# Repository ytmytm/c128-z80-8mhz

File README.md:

# C128 and 8MHz Z80

With a simple daughterboard, a GAL and a 74LS74 the Z80 in C128 can run at dot clock frequency (almost 8MHz) during its 1MHz phase of the system clock, effectively doubling the speed.

Basic benchmarks written in Turbo Pascal show that indeed it is about twice faster.

CP/M is visibly snappier, to the point of being usable.

This circuit works fine, during tests it was stable for several hours, busy with drawing fractals and calculating pi using Monte-Carlo method.

The CPU doesn't even get warm to the touch.

Disk I/O worked fine, as well as REU ram disk M: (emulated by UII+).

## BACKGROUND

There was a message sent to [cbm-hackers mailing list](https://www.softwolves.com/arkiv/cbm-hackers/7/7361.html) back in 2002, about a PCB for C128 that boosted Z80 to 8MHz

Unfortunately that device was not fully reverse-engineered and it seems that it was never mentioned again.

## PREPARING C128

I haven't tried to overclock the original Z80B, I replaced it some time ago by a Z84C0020 that uses much less energy.

Following modifications can be done using bending Z80 pins and soldering to the mainboard, but having a daughterboard will keep everything tidy.

We need to isolate `/WAIT` input (pin 24) from the mainboard because it is tied to `/NMI` there.
We will also disconnected from CPU the onboard `CLK` signal (pin 6).
We will use it as an GAL input to have an option of switching between the original clock (4MHz half of the time) and fast mode (8MHz half of the time).
The new `CLK` will be generated by GAL. We will also use few other lines from Z80 as GAL inputs.

We need two more inputs not available on the Z80 chip/Z80 socket. We want `DOT CLOCK` from the expansion port (pin 6) and the system clock 1MHz signal
(called `CLK1MHZ` below and `D1MHZ` on C128 schematic) from U12 (pin 11).

## OPERATION

This is the normal timing of Z80 in C128. During system clock `CLK1MHZ` low phase VIC generates two clock ticks for Z80.

We use `DOT CLOCK` instead to pass four ticks.

Whenever Z80 wants to read or write to/from memory or I/O we have to stop it until the start of the next 1MHz clock low phase.

Latched data from 74LS74 will hold the `/WAIT` line low until the end of current low phase of `CLK1MHZ` (Z80 turn).
During the following high phase (VIC's turn) 74LS74 will stay in reset and release `WAIT` to inactive (high) state, but during that time we will not output any clock pulses - just like in the original setup.

I had to add a case to `CLKOUT` to handle memory writes. Waitstate is not enough, the CPU had to be really stopped. That's not an issue for reads because they are buffered with U12.

Here is the effect - for two clocks Z80 was running at 1MHz because of memory write, then picked up the speed:

## CIRCUIT

The Kicad project is in [z80-dotclock-gal-and-latch/](z80-dotclock-gal-and-latch) folder.

Schematic is also [available in PDF form](z80-dotclock-gal-and-latch/plots/z80-dot-gal.pdf).

## PCB

Gerber files generated from PCB project that should fit C128 and C128DCR are in  [z80-dotclock-gal-and-latch/gerbers/](z80-dotclock-gal-and-latch/gerbers) folder.

## LOGIC EQUATIONS

PLD file to be used with WinCUPL to generate JED file for programming GAL is available in two versions:

- for 22V10 in [z80-dotclock-gal-and-latch/gal22v10/](z80-dotclock-gal-and-latch/gal22v10/)
- for 16V8 in [z80-dotclock-gal-and-latch/gal6v8/](z80-dotclock-gal-and-latch/gal16v8/)

You will find there all the files generated by WinCUPL, including JED files ready to be flased to GAL devices.

They differ only in pin numbering. I just happened to have an ATF22V10 available.
The circuit is ready for both options - just align pin 1 of 16V8 with pin 1 of the socket.

### 74LS74 and bus timing

Here is how it is supposed to work:

0. VIC cycle phase starts, latch is in reset state, latch `D` input is
   constant `1`, but due to reset `Q` output is `0` and negated `/Q` is `1`; Z80 is
   stopped as its clock is held low
1. Z80 cycle phase starts, latch goes out of reset, `/Q` output = `WAITLATCH`
   stays `1`, Z80 sees that as inactive `/WAIT` and runs program, without bus
   access requests `WAITTRIGGER` stays `0`
2. Z80 wants to access the bus, `WAITTRIGGER` will rise to `1`; this will cause
   latch D input connected to `1` be copied to the output, so `/Q` becomes `0`, Z80
   will see that as an active `/WAIT` and will stop
3. This state will not change until start of the next VIC cycle phase
4. VIC cycle phase starts, latch is reset - will set latch `/Q` to `1`, so for
   Z80 `/WAIT` now becomes inactive; but Z80 won't run because during this
   half-cycle the CPU clock signal is not passed at all
5. Z80 cycle phase starts, it can continue because after latch reset `/WAIT`
   is inactive; Z80 accesses the bus so `WAITTRIGGER` stays `1` until Z80 gets
   what it needs from data lines - then it goes back to `0`

The idea of this is that during Z80 clock phase when `WAITTRIGGER` goes from
inactive to active we can latch `/WAIT` line low to hold it low at least
until the start of VIC cycle.

We release it before/at the start of Z80 cycle it so `/WAIT` becomes high
again - even though the latch trigger condition is still active.

### CLKOUT
The simplest way to handle CLKOUT I did was:
```
  CLKOUT = !DOTCLK & !CLK1MHZ;
```
C128 started fine, but CP/M wouldn't boot. With pieces of Z80 code I was able to confirm that this works for I/O reads and writes but only memory reads.
Memory writes never happened, hence the special case with `MREQ & WR`. 

## 16MHZ?

I tried using the 16MHz clock signal from VDC (pin 2) instead of dot clock.

The C128 will start, but CP/M won't boot. However all my simple tests passed.
I suspect that memory access is still an issue and some of the memory writes fail.

A possible reason is that exact 16MHz signal is not a true double of the dot clock, which depends on PAL/NTSC.

If this is the reason, then one solution could be to [double the dot clock using MAX9010](https://www.analog.com/en/resources/design-notes/simple-circuit-doubles-input-frequency.html).
This idea was [already mentioned on Reddit](https://www.reddit.com/r/c128/comments/9judf7/z80_possible_clockdoubling_mitigation_against/), but that circuit would never work.
But it depends on specific values of R/C pair.

Using a part [specifically designed for that purpose - ICS501](https://www.renesas.com/us/en/document/dst/501-datasheet) seems more reliable.

## OPEN QUESTIONS

1) How can we keep it simple but run at full speed all the time and stall only on memory and I/O access? It's not clear if the device mentioned in 2002 was really working at 8MHz all the time or just during Z80's turn.

2) Since I already used ATF22V10 which has asynchronous reset for registers, it should be possible to get rid of 74LS74 with different assignment of pin 1 (GAL CLK input). I wasn't able to do it.
   I'm probably doing something wrong - messing up high/low vs active/inactive or my CUPL skills are lacking (they are).

3) What is the problem with 16MHz clock? Maybe it should be created by doubling the dot clock to keep things in sync? (No need to bother if (1) is possible).

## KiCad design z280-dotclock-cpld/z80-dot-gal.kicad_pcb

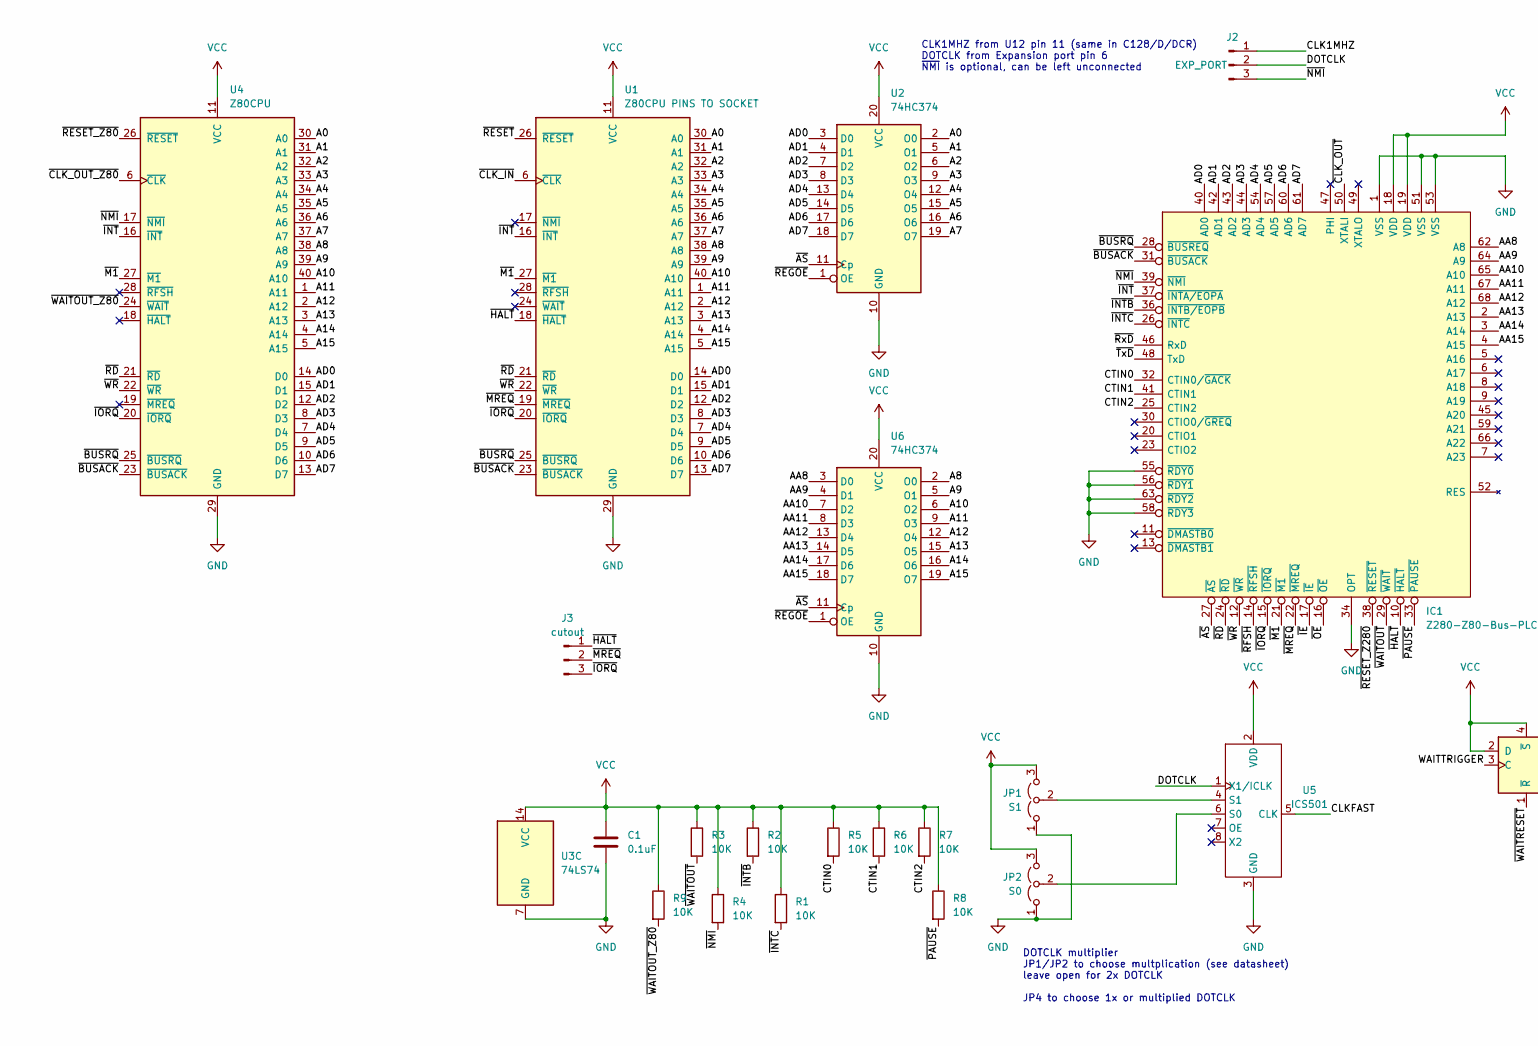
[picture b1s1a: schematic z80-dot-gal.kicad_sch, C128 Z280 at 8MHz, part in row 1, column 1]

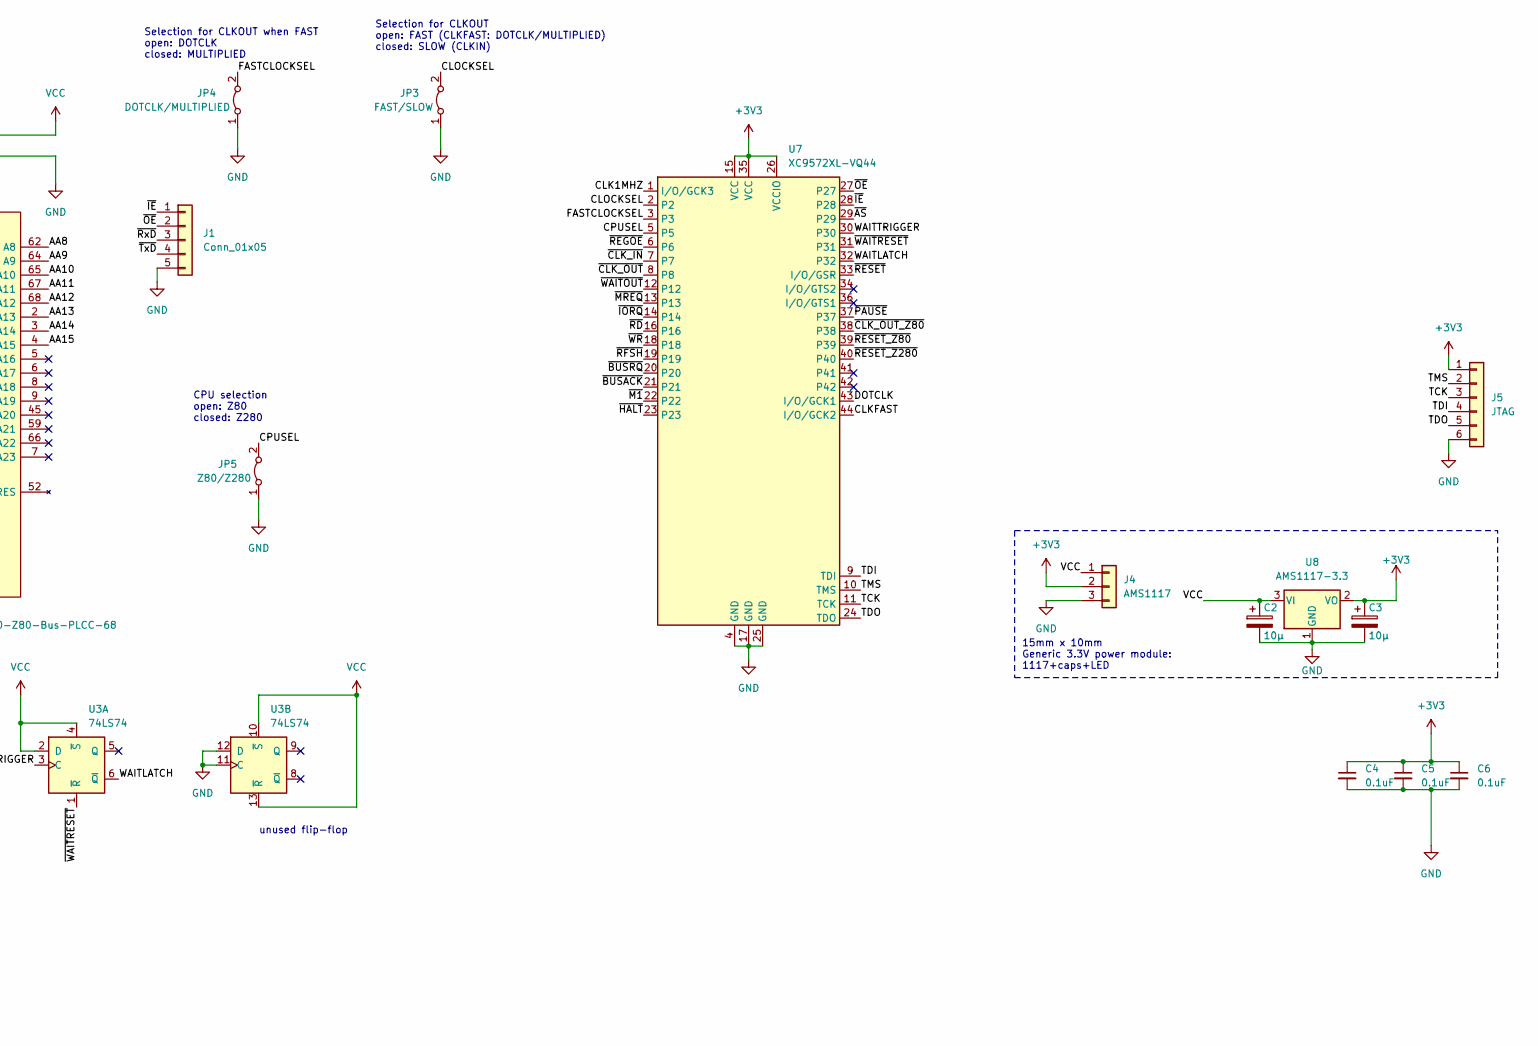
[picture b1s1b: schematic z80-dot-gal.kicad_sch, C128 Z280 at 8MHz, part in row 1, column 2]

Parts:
C1: 0.1uF; C_Disc_D8.0mm_W2.5mm_P5.00mm
C2, C3: 10µ; CP_EIA-3216-12_Kemet-S_HandSolder; JLCPCB Part # C1969735
C4, C5, C6: 0.1uF; C_0805_2012Metric_Pad1.18x1.45mm_HandSolder; JLCPCB Part # C49678
IC1: Z280-Z80-Bus-PLCC-68; PLCC-68_THT-Socket; Manufacturer_Part_Number Z8S18033VSG; Mouser Part Number 692-Z8S18033VSG
J1: Conn_01x05; PinHeader_1x05_P2.54mm_Vertical
J2: EXP_PORT; PinHeader_1x03_P2.54mm_Vertical
J3: cutout; PinHeader_1x03_P2.54mm_Vertical
J4: AMS1117; PinHeader_1x03_P2.54mm_Vertical
J5: JTAG; PinHeader_1x06_P2.54mm_Vertical
JP1: S1; PinHeader_1x03_P2.54mm_Vertical
JP2: S0; PinHeader_1x03_P2.54mm_Vertical
JP3: FAST/SLOW; PinHeader_1x02_P2.54mm_Vertical
JP4: DOTCLK/MULTIPLIED; PinHeader_1x02_P2.54mm_Vertical
JP5: Z80/Z280; PinHeader_1x02_P2.54mm_Vertical
R1, R2, R3, R4, R5, R6, R7, R8, R9: 10K; R_0805_2012Metric_Pad1.20x1.40mm_HandSolder
U1: Z80CPU PINS TO SOCKET; DIP-40_W15.24mm_Socket_LongPads
U2, U6: 74HC374; DIP-20_W7.62mm
U3: 74LS74; DIP-14_W7.62mm_Socket
U4: Z80CPU; DIP-40_W15.24mm_Socket_LongPads
U5: ICS501; SOIC-8_3.9x4.9mm_P1.27mm
U7: XC9572XL-VQ44; TQFP-44_10x10mm_P0.8mm
U8: AMS1117-3.3; SOT-223-3_TabPin2; JLCPCB Part # C6186

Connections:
+3V3: C3.1, C4.1, C5.1, C6.1, J4.2, J5.1, U7.15 (VCC), U7.26 (VCCIO), U7.35 (VCC), U8.2 (VO)
/A0: U1.30 (A0), U2.2 (O0), U4.30 (A0)
/A1: U1.31 (A1), U2.5 (O1), U4.31 (A1)
/A2: U1.32 (A2), U2.6 (O2), U4.32 (A2)
/A3: U1.33 (A3), U2.9 (O3), U4.33 (A3)
/A4: U1.34 (A4), U2.12 (O4), U4.34 (A4)
/A5: U1.35 (A5), U2.15 (O5), U4.35 (A5)
/A6: U1.36 (A6), U2.16 (O6), U4.36 (A6)
/A7: U1.37 (A7), U2.19 (O7), U4.37 (A7)
/A8: U1.38 (A8), U4.38 (A8), U6.2 (O0)
/A9: U1.39 (A9), U4.39 (A9), U6.5 (O1)
/A10: U1.40 (A10), U4.40 (A10), U6.6 (O2)
/A11: U1.1 (A11), U4.1 (A11), U6.9 (O3)
/A12: U1.2 (A12), U4.2 (A12), U6.12 (O4)
/A13: U1.3 (A13), U4.3 (A13), U6.15 (O5)
/A14: U1.4 (A14), U4.4 (A14), U6.16 (O6)
/A15: U1.5 (A15), U4.5 (A15), U6.19 (O7)
/AA8: IC1.62 (A8), U6.3 (D0)
/AA9: IC1.64 (A9), U6.4 (D1)
/AA10: IC1.65 (A10), U6.7 (D2)
/AA11: IC1.67 (A11), U6.8 (D3)
/AA12: IC1.68 (A12), U6.13 (D4)
/AA13: IC1.2 (A13), U6.14 (D5)
/AA14: IC1.3 (A14), U6.17 (D6)
/AA15: IC1.4 (A15), U6.18 (D7)
/AD0: IC1.40 (AD0), U1.14 (D0), U2.3 (D0), U4.14 (D0)
/AD1: IC1.42 (AD1), U1.15 (D1), U2.4 (D1), U4.15 (D1)
/AD2: IC1.43 (AD2), U1.12 (D2), U2.7 (D2), U4.12 (D2)
/AD3: IC1.44 (AD3), U1.8 (D3), U2.8 (D3), U4.8 (D3)
/AD4: IC1.54 (AD4), U1.7 (D4), U2.13 (D4), U4.7 (D4)
/AD5: IC1.57 (AD5), U1.9 (D5), U2.14 (D5), U4.9 (D5)
/AD6: IC1.60 (AD6), U1.10 (D6), U2.17 (D6), U4.10 (D6)
/AD7: IC1.61 (AD7), U1.13 (D7), U2.18 (D7), U4.13 (D7)
/CLK1MHZ: J2.1, U7.1 (I/O/GCK3)
/CLKFAST: U5.5 (CLK), U7.44 (I/O/GCK2)
/CLOCKSEL: JP3.2 (B), U7.2
/CPUSEL: JP5.2 (B), U7.5
/CTIN0: IC1.32 (CTIN0/~GACK), R5.2
/CTIN1: IC1.41 (CTIN1), R6.2
/CTIN2: IC1.25 (CTIN2), R7.2
/DOTCLK: J2.2, U5.1 (X1/ICLK), U7.43 (I/O/GCK1)
/FASTCLOCKSEL: JP4.2 (B), U7.3
/TCK: J5.3, U7.11 (TCK)
/TDI: J5.4, U7.9 (TDI)
/TDO: J5.5, U7.24 (TDO)
/TMS: J5.2, U7.10 (TMS)
/WAITLATCH: U3.6 (~Q), U7.32
/WAITTRIGGER: U3.3 (C), U7.30
/~AS: IC1.27 (~AS), U2.11 (Cp), U6.11 (Cp), U7.29
/~BUSACK: IC1.31 (~BUSACK), U1.23 (~BUSACK), U4.23 (~BUSACK), U7.21
/~BUSRQ: IC1.28 (~BUSREQ), U1.25 (~BUSRQ), U4.25 (~BUSRQ), U7.20
/~CLK_IN: U1.6 (~CLK), U7.7
/~CLK_OUT_Z80: U4.6 (~CLK), U7.38
/~CLK_OUT: IC1.50 (XTALI), U7.8
/~HALT: IC1.10 (~HALT), J3.1, U1.18 (~HALT), U7.23
/~IE: IC1.17 (~IE), J1.1, U7.28
/~INTB: IC1.36 (~INTB/EOPB), R2.2
/~INTC: IC1.26 (~INTC), R1.2
/~INT: IC1.37 (~INTA/EOPA), U1.16 (~INT), U4.16 (~INT)
/~IORQ: IC1.15 (~IORQ), J3.3, U1.20 (~IORQ), U4.20 (~IORQ), U7.14
/~M1: IC1.21 (~M1), U1.27 (~M1), U4.27 (~M1), U7.22
/~MREQ: IC1.22 (~MREQ), J3.2, U1.19 (~MREQ), U7.13
/~NMI: IC1.39 (~NMI), J2.3, R4.2, U4.17 (~NMI)
/~OE: IC1.16 (~OE), J1.2, U7.27
/~PAUSE: IC1.33 (~PAUSE), R8.2, U7.37
/~RD: IC1.24 (~RD), U1.21 (~RD), U4.21 (~RD), U7.16
/~REGOE: U2.1 (OE), U6.1 (OE), U7.6
/~RESET_Z80: U4.26 (~RESET), U7.39
/~RESET_Z280: IC1.38 (~RESET), U7.40
/~RESET: U1.26 (~RESET), U7.33 (I/O/GSR)
/~RFSH: IC1.14 (~RFSH), U7.19
/~RxD: IC1.46 (RxD), J1.3
/~TxD: IC1.48 (TxD), J1.4
/~WAITOUT_Z80: R9.2, U4.24 (~WAIT)
/~WAITOUT: IC1.29 (~WAIT), R3.2, U7.12
/~WAITRESET: U3.1 (~R), U7.31
/~WR: IC1.12 (~WR), U1.22 (~WR), U4.22 (~WR), U7.18
GND: C1.2, C2.2, C3.2, C4.2, C5.2, C6.2, IC1.1 (VSS), IC1.34 (OPT), IC1.51 (VSS), IC1.53 (VSS), IC1.55 (~RDY0), IC1.56 (~RDY1), IC1.58 (~RDY3), IC1.63 (~RDY2), J1.5, J4.3, J5.6, JP1.1 (A), JP2.1 (A), JP3.1 (A), JP4.1 (A), JP5.1 (A), U1.29 (GND), U2.10 (GND), U3.7 (GND), U3.11 (C), U3.12 (D), U4.29 (GND), U5.3 (GND), U6.10 (GND), U7.4 (GND), U7.17 (GND), U7.25 (GND), U8.1 (GND)
unnamed: JP1.2 (C), U5.4 (S1)
unnamed: JP2.2 (C), U5.6 (S0)
VCC: C1.1, C2.1, IC1.18 (VDD), IC1.19 (VDD), J4.1, JP1.3 (B), JP2.3 (B), R1.1, R2.1, R3.1, R4.1, R5.1, R6.1, R7.1, R8.1, R9.1, U1.11 (VCC), U2.20 (VCC), U3.2 (D), U3.4 (~S), U3.10 (~S), U3.13 (~R), U3.14 (VCC), U4.11 (VCC), U5.2 (VDD), U6.20 (VCC), U8.3 (VI)

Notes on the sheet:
CLK1MHZ from U12 pin 11 (same in C128/D/DCR) DOTCLK from Expansion port pin 6 ~{NMI} is optional, can be left unconnected
15mm x 10mm Generic 3.3V power module: 1117+caps+LED
DOTCLK multiplier JP1/JP2 to choose multplication (see datasheet) leave open for 2x DOTCLK JP4 to choose 1x or multiplied DOTCLK
CPU selection open: Z80 closed: Z280
Selection for CLKOUT open: FAST (CLKFAST: DOTCLK/MULTIPLIED) closed: SLOW (CLKIN)
unused flip-flop
Selection for CLKOUT when FAST open: DOTCLK closed: MULTIPLIED

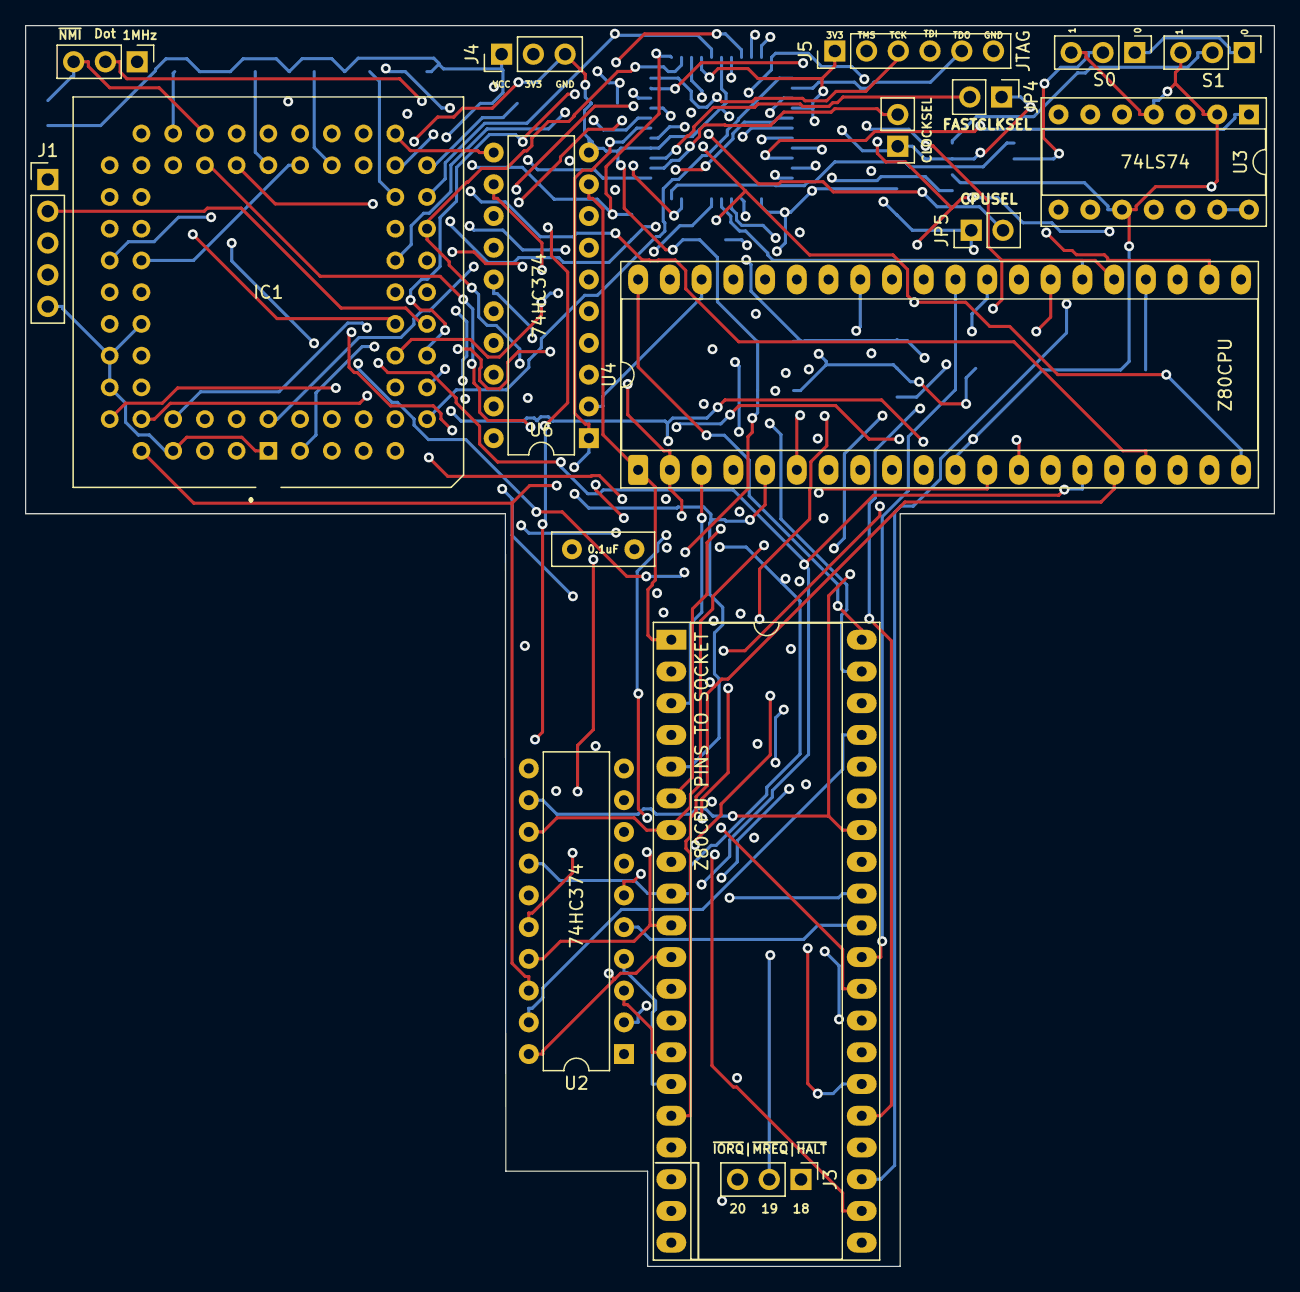
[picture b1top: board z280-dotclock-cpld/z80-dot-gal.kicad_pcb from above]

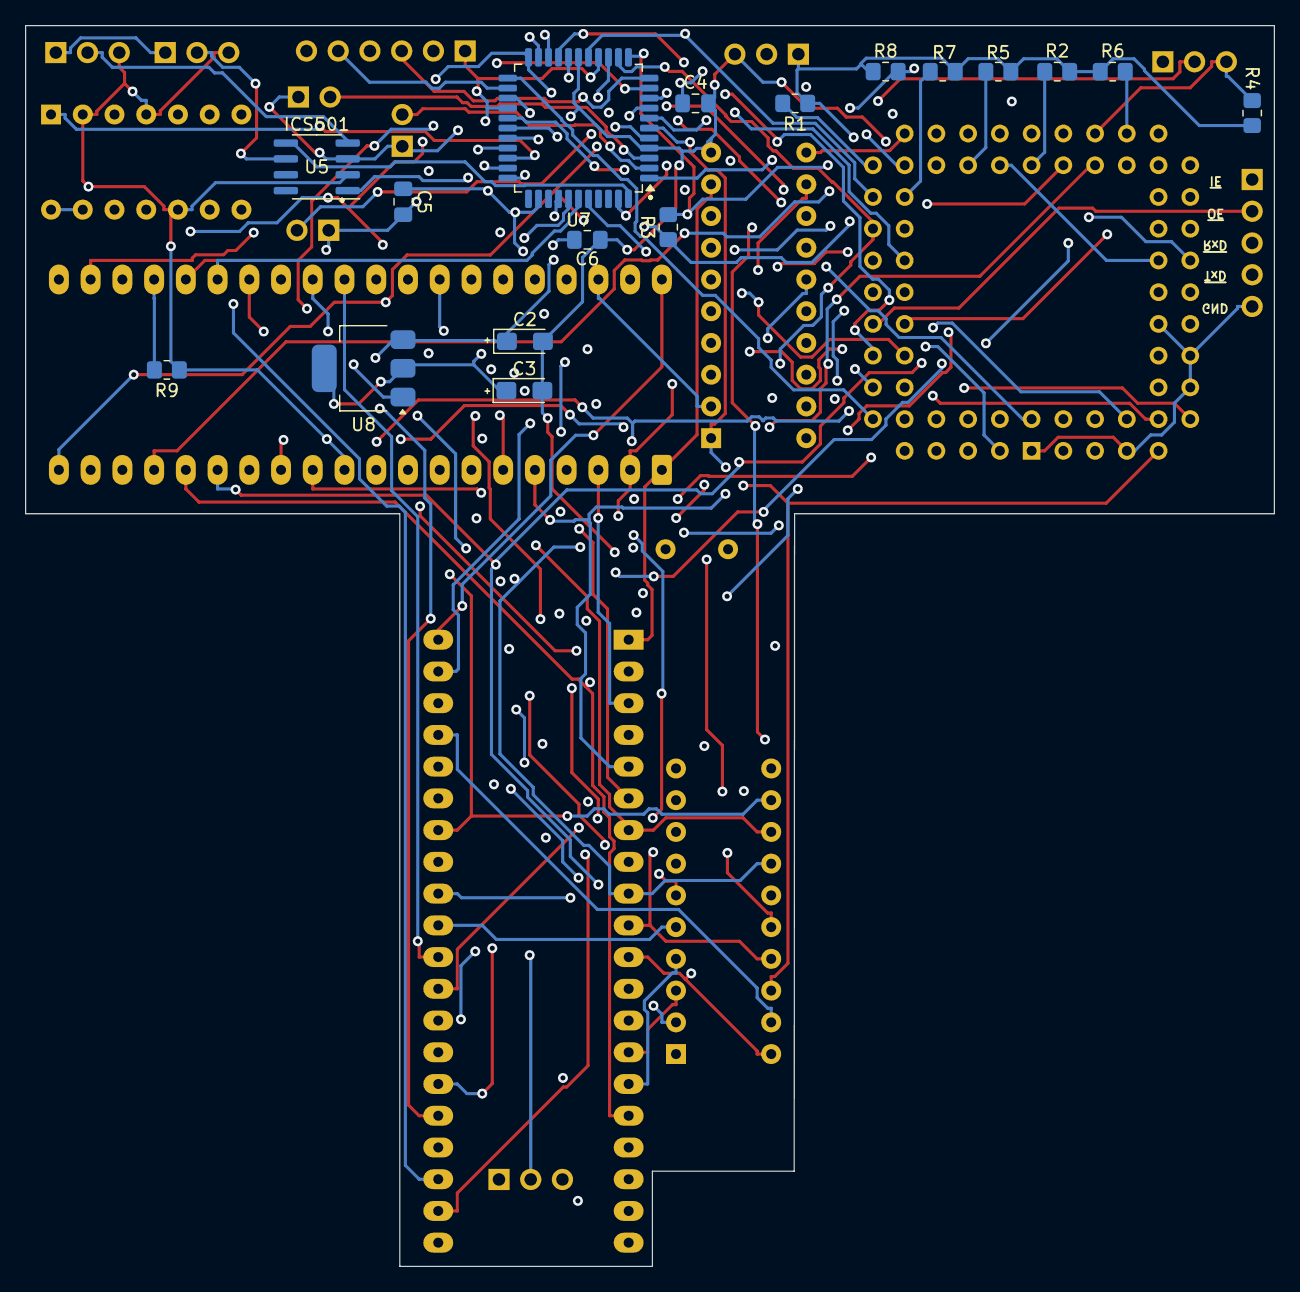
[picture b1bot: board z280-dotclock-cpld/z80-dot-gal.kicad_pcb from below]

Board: 4 copper layers, 100.0 x 99.3 mm, 34 parts (17 on the bottom side), 81 nets.

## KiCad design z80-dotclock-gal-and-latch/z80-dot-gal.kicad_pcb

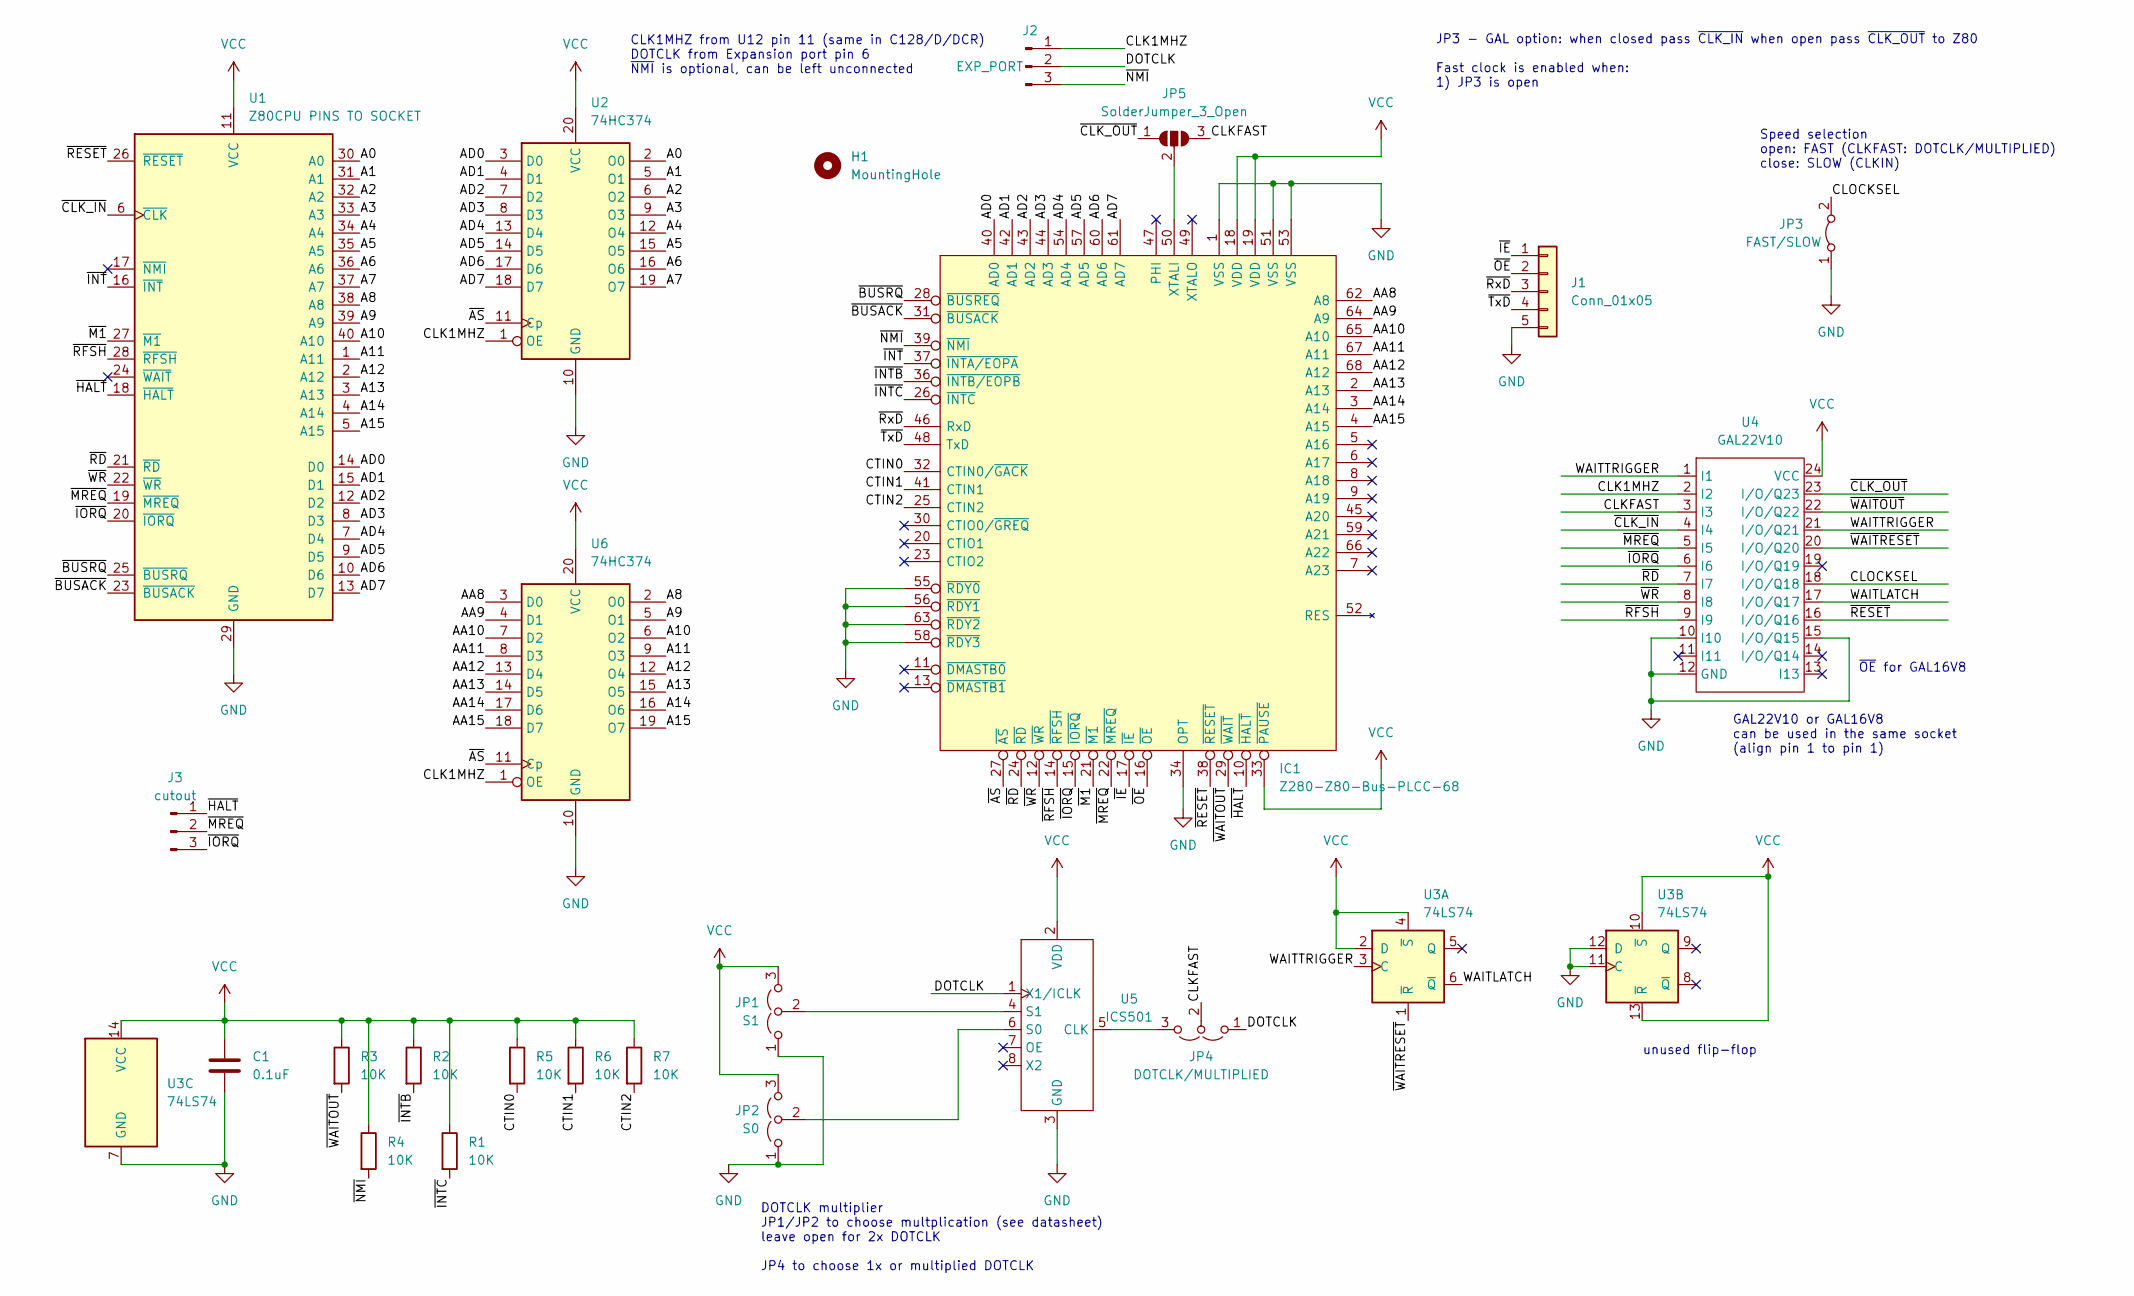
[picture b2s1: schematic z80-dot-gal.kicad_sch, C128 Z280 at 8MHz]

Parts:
C1: 0.1uF; C_Disc_D8.0mm_W2.5mm_P5.00mm
H1: MountingHole; MountingHole_2.5mm
IC1: Z280-Z80-Bus-PLCC-68; PLCC-68_THT-Socket; Manufacturer_Part_Number Z8S18033VSG; Mouser Part Number 692-Z8S18033VSG
J1: Conn_01x05; PinHeader_1x05_P2.54mm_Vertical
J2: EXP_PORT; PinHeader_1x03_P2.54mm_Vertical
J3: cutout; PinHeader_1x03_P2.54mm_Vertical
JP1: S1; PinHeader_1x03_P2.54mm_Vertical
JP2: S0; PinHeader_1x03_P2.54mm_Vertical
JP3: FAST/SLOW; PinHeader_1x02_P2.54mm_Vertical
JP4: DOTCLK/MULTIPLIED; PinHeader_1x03_P2.54mm_Vertical
JP5: SolderJumper_3_Open; PinHeader_1x03_P2.54mm_Vertical
R1, R2, R3, R4, R5, R6, R7: 10K; R_0805_2012Metric_Pad1.20x1.40mm_HandSolder
U1: Z80CPU PINS TO SOCKET; DIP-40_W15.24mm_Socket_LongPads
U2, U6: 74HC374; DIP-20_W7.62mm
U3: 74LS74; DIP-14_W7.62mm_Socket
U4: GAL22V10; DIP-24_W7.62mm_Socket
U5: ICS501; SOIC-8_3.9x4.9mm_P1.27mm

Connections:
/A0: U1.30 (A0), U2.2 (O0)
/A1: U1.31 (A1), U2.5 (O1)
/A2: U1.32 (A2), U2.6 (O2)
/A3: U1.33 (A3), U2.9 (O3)
/A4: U1.34 (A4), U2.12 (O4)
/A5: U1.35 (A5), U2.15 (O5)
/A6: U1.36 (A6), U2.16 (O6)
/A7: U1.37 (A7), U2.19 (O7)
/A8: U1.38 (A8), U6.2 (O0)
/A9: U1.39 (A9), U6.5 (O1)
/A10: U1.40 (A10), U6.6 (O2)
/A11: U1.1 (A11), U6.9 (O3)
/A12: U1.2 (A12), U6.12 (O4)
/A13: U1.3 (A13), U6.15 (O5)
/A14: U1.4 (A14), U6.16 (O6)
/A15: U1.5 (A15), U6.19 (O7)
/AA8: IC1.62 (A8), U6.3 (D0)
/AA9: IC1.64 (A9), U6.4 (D1)
/AA10: IC1.65 (A10), U6.7 (D2)
/AA11: IC1.67 (A11), U6.8 (D3)
/AA12: IC1.68 (A12), U6.13 (D4)
/AA13: IC1.2 (A13), U6.14 (D5)
/AA14: IC1.3 (A14), U6.17 (D6)
/AA15: IC1.4 (A15), U6.18 (D7)
/AD0: IC1.40 (AD0), U1.14 (D0), U2.3 (D0)
/AD1: IC1.42 (AD1), U1.15 (D1), U2.4 (D1)
/AD2: IC1.43 (AD2), U1.12 (D2), U2.7 (D2)
/AD3: IC1.44 (AD3), U1.8 (D3), U2.8 (D3)
/AD4: IC1.54 (AD4), U1.7 (D4), U2.13 (D4)
/AD5: IC1.57 (AD5), U1.9 (D5), U2.14 (D5)
/AD6: IC1.60 (AD6), U1.10 (D6), U2.17 (D6)
/AD7: IC1.61 (AD7), U1.13 (D7), U2.18 (D7)
/CLK1MHZ: J2.1, U2.1 (OE), U4.2 (I2), U6.1 (OE)
/CLKFAST: JP4.2 (C), JP5.3 (B), U4.3 (I3)
/CLOCKSEL: JP3.2 (B), U4.18 (I/O/Q18)
/CTIN0: IC1.32 (CTIN0/~GACK), R5.2
/CTIN1: IC1.41 (CTIN1), R6.2
/CTIN2: IC1.25 (CTIN2), R7.2
/DOTCLK: J2.2, JP4.1 (A), U5.1 (X1/ICLK)
/WAITLATCH: U3.6 (~Q), U4.17 (I/O/Q17)
/WAITTRIGGER: U3.3 (C), U4.1 (I1), U4.21 (I/O/Q21)
/~AS: IC1.27 (~AS), U2.11 (Cp), U6.11 (Cp)
/~BUSACK: IC1.31 (~BUSACK), U1.23 (~BUSACK)
/~BUSRQ: IC1.28 (~BUSREQ), U1.25 (~BUSRQ)
/~CLK_IN: U1.6 (~CLK), U4.4 (I4)
/~CLK_OUT: JP5.1 (A), U4.23 (I/O/Q23)
/~HALT: IC1.10 (~HALT), J3.1, U1.18 (~HALT)
/~IE: IC1.17 (~IE), J1.1
/~INTB: IC1.36 (~INTB/EOPB), R2.2
/~INTC: IC1.26 (~INTC), R1.2
/~INT: IC1.37 (~INTA/EOPA), U1.16 (~INT)
/~IORQ: IC1.15 (~IORQ), J3.3, U1.20 (~IORQ), U4.6 (I6)
/~M1: IC1.21 (~M1), U1.27 (~M1)
/~MREQ: IC1.22 (~MREQ), J3.2, U1.19 (~MREQ), U4.5 (I5)
/~NMI: IC1.39 (~NMI), J2.3, R4.2
/~OE: IC1.16 (~OE), J1.2
/~RD: IC1.24 (~RD), U1.21 (~RD), U4.7 (I7)
/~RESET: IC1.38 (~RESET), U1.26 (~RESET), U4.16 (I/O/Q16)
/~RFSH: IC1.14 (~RFSH), U1.28 (~RFSH), U4.9 (I9)
/~RxD: IC1.46 (RxD), J1.3
/~TxD: IC1.48 (TxD), J1.4
/~WAITOUT: IC1.29 (~WAIT), R3.2, U4.22 (I/O/Q22)
/~WAITRESET: U3.1 (~R), U4.20 (I/O/Q20)
/~WR: IC1.12 (~WR), U1.22 (~WR), U4.8 (I8)
GND: C1.2, IC1.1 (VSS), IC1.34 (OPT), IC1.51 (VSS), IC1.53 (VSS), IC1.55 (~RDY0), IC1.56 (~RDY1), IC1.58 (~RDY3), IC1.63 (~RDY2), J1.5, JP1.1 (A), JP2.1 (A), JP3.1 (A), U1.29 (GND), U2.10 (GND), U3.7 (GND), U3.11 (C), U3.12 (D), U4.10 (I10), U4.12 (GND), U4.15 (I/O/Q15), U5.3 (GND), U6.10 (GND)
unnamed: IC1.50 (XTALI), JP5.2 (C)
unnamed: JP1.2 (C), U5.4 (S1)
unnamed: JP2.2 (C), U5.6 (S0)
unnamed: JP4.3 (B), U5.5 (CLK)
VCC: C1.1, IC1.18 (VDD), IC1.19 (VDD), IC1.33 (~PAUSE), JP1.3 (B), JP2.3 (B), R1.1, R2.1, R3.1, R4.1, R5.1, R6.1, R7.1, U1.11 (VCC), U2.20 (VCC), U3.2 (D), U3.4 (~S), U3.10 (~S), U3.13 (~R), U3.14 (VCC), U4.24 (VCC), U5.2 (VDD), U6.20 (VCC)

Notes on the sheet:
GAL22V10 or GAL16V8 can be used in the same socket (align pin 1 to pin 1)
CLK1MHZ from U12 pin 11 (same in C128/D/DCR) DOTCLK from Expansion port pin 6 ~{NMI} is optional, can be left unconnected
DOTCLK multiplier JP1/JP2 to choose multplication (see datasheet) leave open for 2x DOTCLK JP4 to choose 1x or multiplied DOTCLK
JP3 - GAL option: when closed pass ~{CLK_IN} when open pass ~{CLK_OUT} to Z80 Fast clock is enabled when: 1) JP3 is open
Speed selection open: FAST (CLKFAST: DOTCLK/MULTIPLIED) close: SLOW (CLKIN)
~{OE} for GAL16V8
unused flip-flop

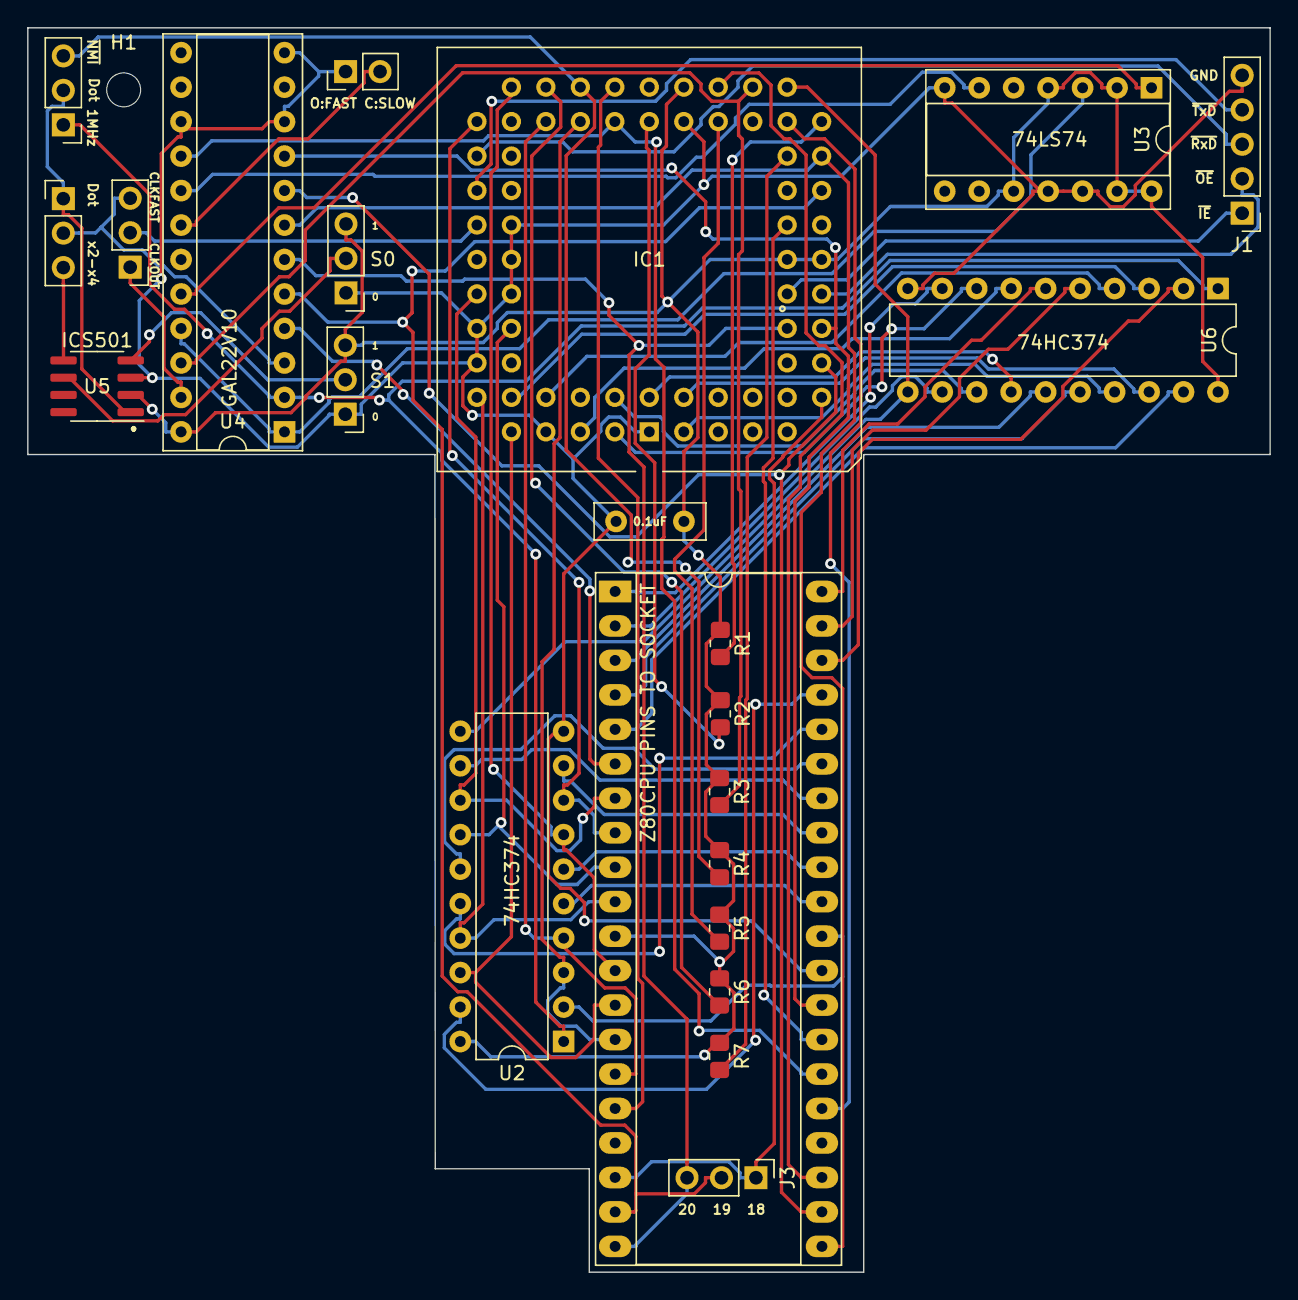
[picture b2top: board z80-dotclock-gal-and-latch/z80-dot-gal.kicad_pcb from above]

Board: 2 copper layers, 91.5 x 91.7 mm, 24 parts (0 on the bottom side), 70 nets.

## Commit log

2024-06-01 initial import
2024-06-03 Schematic revision v2, without PCB: - remove test pads - remove unused connections to GAL pins 6-8 - add J3 and lots of descriptions - add required connects to /WR, /RESET, /RFSH - make GAL socket co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
2024-06-03 updated comments and pin assignment to make the most of V1 PCB compatible with GAL16V8 (renumber output pins)
2024-06-03 schematic v2 plot
2024-06-03 media
2024-06-03 correct descriptions
2024-06-07 move to gal22v10/
2024-06-07 gal16v8 pin numbers
2024-06-07 all WinCUPL files generated for both options 22v10 and 16v8
2024-06-07 update about GAL/PLD/JED
2024-06-07 C128D/DCR PCB project (without cutout for 256k MMU expansion)
2024-06-07 ignored files
2024-06-19 rev 2.1 development board with ICS501 clock multiplier and reordered GAL inputs
2024-06-19 update to new board revision, no change with latch yet
2024-07-14 updated for pins assigned according to v2.1 PCB
2024-10-09 Z280 option; parts from https://github.com/flypie/Z80-CPU-for-KiCAD.git based on https://github.com/Plasmode/ZZ80RC
2026-02-09 Z280 board with CPLD for more testing options AND Z80 fallback (to regain control for 6502) - too big for C128DCR, can only fit in C128D w/o a case - no CPLD firmware yet
2026-02-09 4-layer development version sent for fabrication
